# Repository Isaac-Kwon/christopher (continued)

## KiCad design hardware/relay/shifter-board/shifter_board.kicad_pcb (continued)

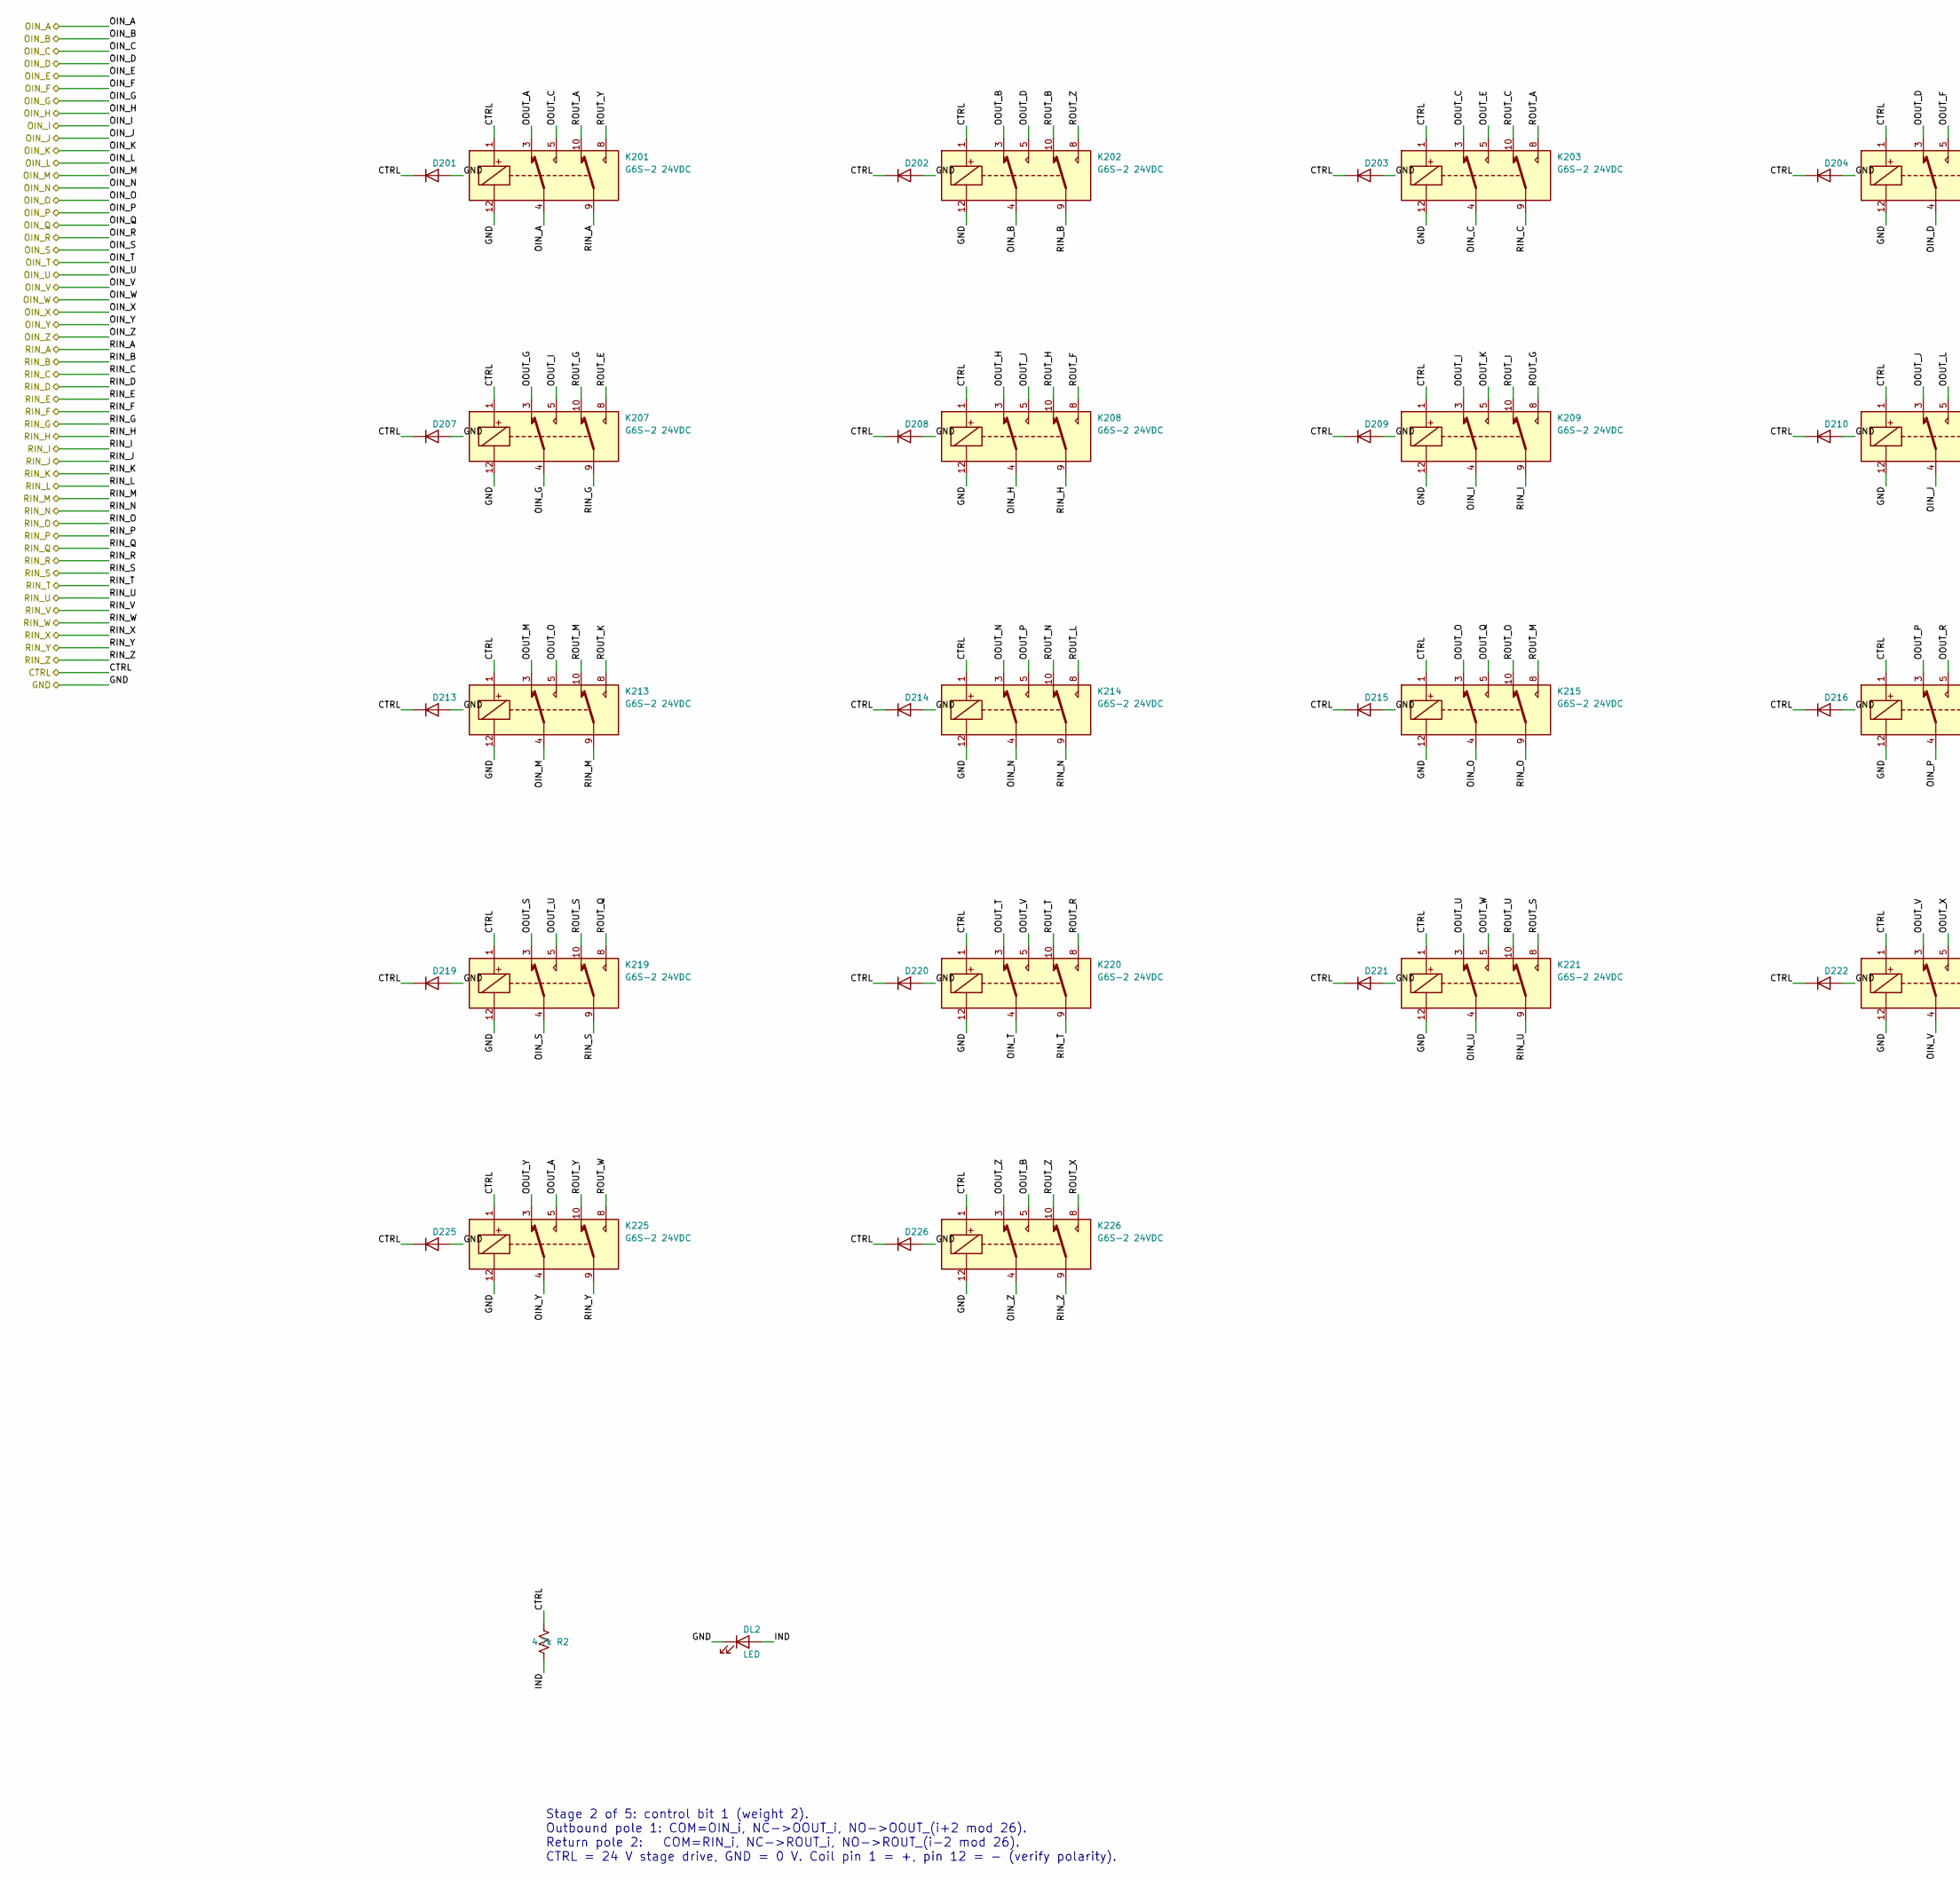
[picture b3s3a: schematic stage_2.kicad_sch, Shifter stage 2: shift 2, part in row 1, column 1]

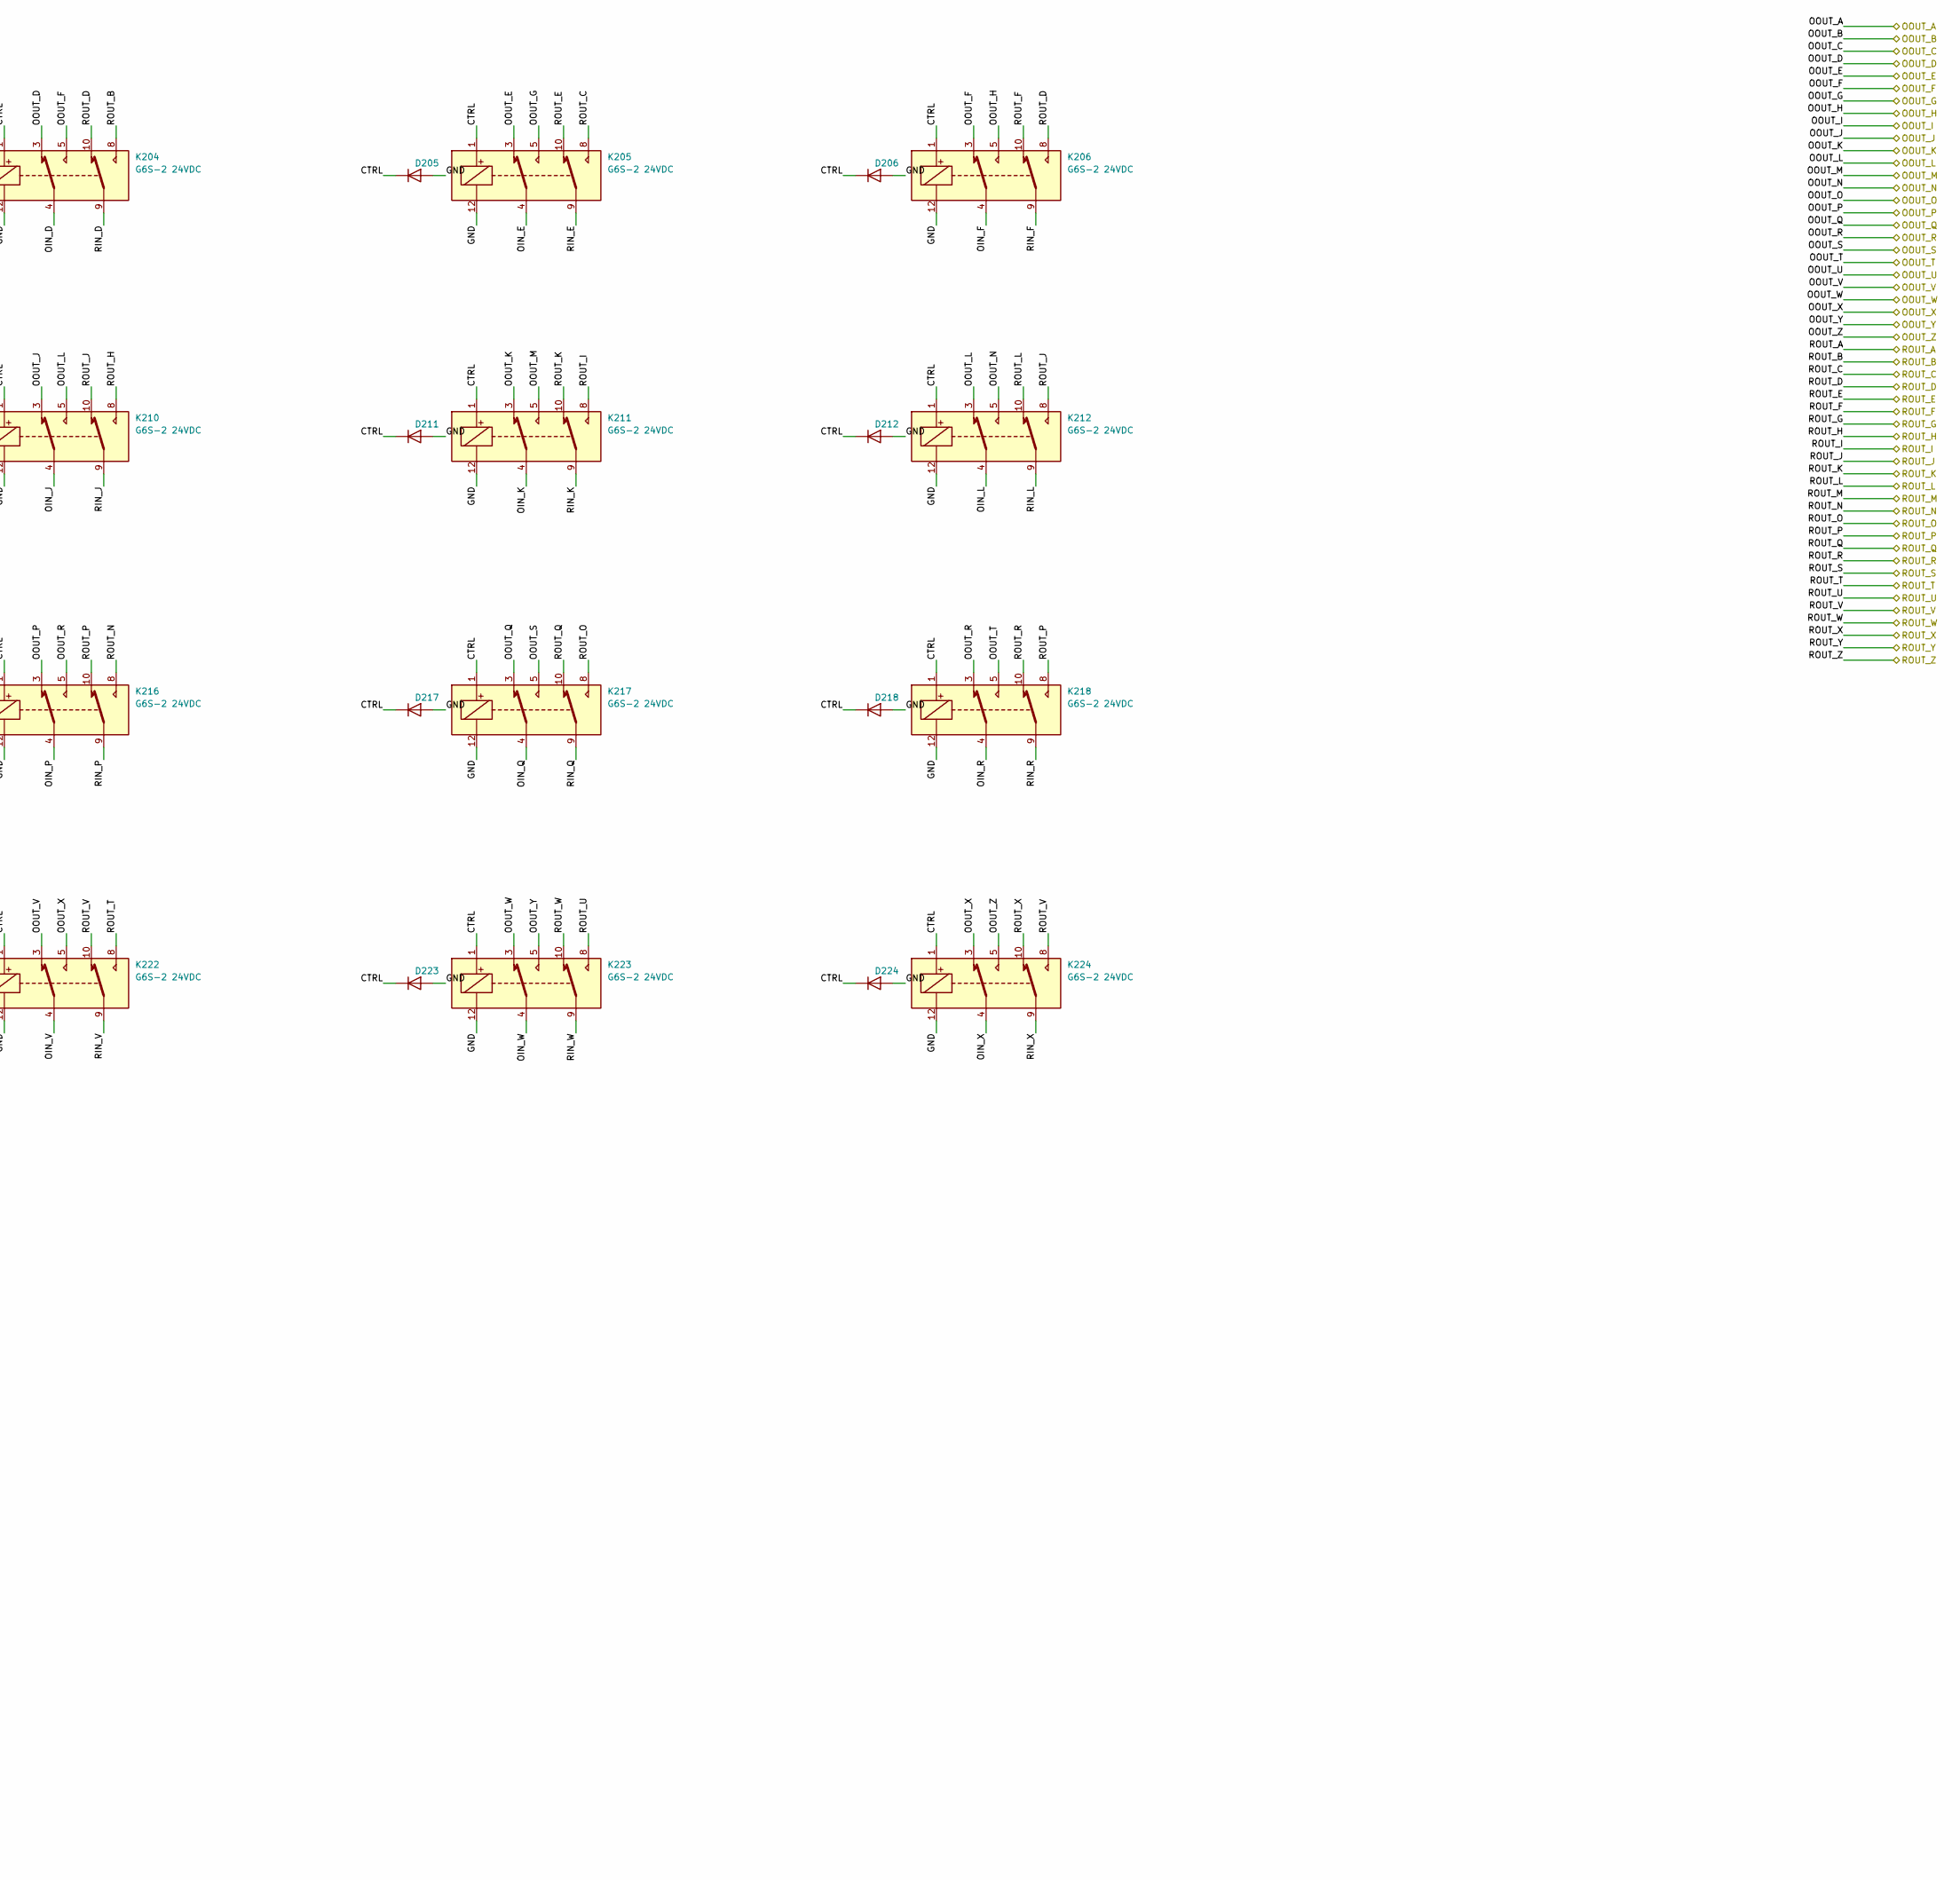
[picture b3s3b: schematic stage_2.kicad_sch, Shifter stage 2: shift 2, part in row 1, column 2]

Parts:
D201, D202, D203, D204, D205, D206, D207, D208, D209, D210, D211, D212, D213, D214, D215, D216, D217, D218, D219, D220, D221, D222, D223, D224, D225, D226: 1N4148W; D_SOD-123
DL2: LED; LED_0603_1608Metric
K201, K202, K203, K204, K205, K206, K207, K208, K209, K210, K211, K212, K213, K214, K215, K216, K217, K218, K219, K220, K221, K222, K223, K224, K225, K226: G6S-2 24VDC; Relay_DPDT_Omron_G6S-2
R2: 4.7k; R_0603_1608Metric

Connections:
/CTRL1: D201.1 (K), D202.1 (K), D203.1 (K), D204.1 (K), D205.1 (K), D206.1 (K), D207.1 (K), D208.1 (K), D209.1 (K), D210.1 (K), D211.1 (K), D212.1 (K), D213.1 (K), D214.1 (K), D215.1 (K), D216.1 (K), D217.1 (K), D218.1 (K), D219.1 (K), D220.1 (K), D221.1 (K), D222.1 (K), D223.1 (K), D224.1 (K), D225.1 (K), D226.1 (K), K201.1, K202.1, K203.1, K204.1, K205.1, K206.1, K207.1, K208.1, K209.1, K210.1, K211.1, K212.1, K213.1, K214.1, K215.1, K216.1, K217.1, K218.1, K219.1, K220.1, K221.1, K222.1, K223.1, K224.1, K225.1, K226.1, R2.1; also elsewhere on the board
/GND: D201.2 (A), D202.2 (A), D203.2 (A), D204.2 (A), D205.2 (A), D206.2 (A), D207.2 (A), D208.2 (A), D209.2 (A), D210.2 (A), D211.2 (A), D212.2 (A), D213.2 (A), D214.2 (A), D215.2 (A), D216.2 (A), D217.2 (A), D218.2 (A), D219.2 (A), D220.2 (A), D221.2 (A), D222.2 (A), D223.2 (A), D224.2 (A), D225.2 (A), D226.2 (A), DL2.1 (K), K201.12, K202.12, K203.12, K204.12, K205.12, K206.12, K207.12, K208.12, K209.12, K210.12, K211.12, K212.12, K213.12, K214.12, K215.12, K216.12, K217.12, K218.12, K219.12, K220.12, K221.12, K222.12, K223.12, K224.12, K225.12, K226.12; also elsewhere on the board
/O1_A: K201.4; also elsewhere on the board
/O1_B: K202.4; also elsewhere on the board
/O1_C: K203.4; also elsewhere on the board
/O1_D: K204.4; also elsewhere on the board
/O1_E: K205.4; also elsewhere on the board
/O1_F: K206.4; also elsewhere on the board
/O1_G: K207.4; also elsewhere on the board
/O1_H: K208.4; also elsewhere on the board
/O1_I: K209.4; also elsewhere on the board
/O1_J: K210.4; also elsewhere on the board
/O1_K: K211.4; also elsewhere on the board
/O1_L: K212.4; also elsewhere on the board
/O1_M: K213.4; also elsewhere on the board
/O1_N: K214.4; also elsewhere on the board
/O1_O: K215.4; also elsewhere on the board
/O1_P: K216.4; also elsewhere on the board
/O1_Q: K217.4; also elsewhere on the board
/O1_R: K218.4; also elsewhere on the board
/O1_S: K219.4; also elsewhere on the board
/O1_T: K220.4; also elsewhere on the board
/O1_U: K221.4; also elsewhere on the board
/O1_V: K222.4; also elsewhere on the board
/O1_W: K223.4; also elsewhere on the board
/O1_X: K224.4; also elsewhere on the board
/O1_Y: K225.4; also elsewhere on the board
/O1_Z: K226.4; also elsewhere on the board
/O2_A: K201.3, K225.5; also elsewhere on the board
/O2_B: K202.3, K226.5; also elsewhere on the board
/O2_C: K201.5, K203.3; also elsewhere on the board
/O2_D: K202.5, K204.3; also elsewhere on the board
/O2_E: K203.5, K205.3; also elsewhere on the board
/O2_F: K204.5, K206.3; also elsewhere on the board
/O2_G: K205.5, K207.3; also elsewhere on the board
/O2_H: K206.5, K208.3; also elsewhere on the board
/O2_I: K207.5, K209.3; also elsewhere on the board
/O2_J: K208.5, K210.3; also elsewhere on the board
/O2_K: K209.5, K211.3; also elsewhere on the board
/O2_L: K210.5, K212.3; also elsewhere on the board
/O2_M: K211.5, K213.3; also elsewhere on the board
/O2_N: K212.5, K214.3; also elsewhere on the board
/O2_O: K213.5, K215.3; also elsewhere on the board
/O2_P: K214.5, K216.3; also elsewhere on the board
/O2_Q: K215.5, K217.3; also elsewhere on the board
/O2_R: K216.5, K218.3; also elsewhere on the board
/O2_S: K217.5, K219.3; also elsewhere on the board
/O2_T: K218.5, K220.3; also elsewhere on the board
/O2_U: K219.5, K221.3; also elsewhere on the board
/O2_V: K220.5, K222.3; also elsewhere on the board
/O2_W: K221.5, K223.3; also elsewhere on the board
/O2_X: K222.5, K224.3; also elsewhere on the board
/O2_Y: K223.5, K225.3; also elsewhere on the board
/O2_Z: K224.5, K226.3; also elsewhere on the board
/R1_A: K201.9; also elsewhere on the board
/R1_B: K202.9; also elsewhere on the board
/R1_C: K203.9; also elsewhere on the board
/R1_D: K204.9; also elsewhere on the board
/R1_E: K205.9; also elsewhere on the board
/R1_F: K206.9; also elsewhere on the board
/R1_G: K207.9; also elsewhere on the board
/R1_H: K208.9; also elsewhere on the board
/R1_I: K209.9; also elsewhere on the board
/R1_J: K210.9; also elsewhere on the board
/R1_K: K211.9; also elsewhere on the board
/R1_L: K212.9; also elsewhere on the board
/R1_M: K213.9; also elsewhere on the board
/R1_N: K214.9; also elsewhere on the board
/R1_O: K215.9; also elsewhere on the board
/R1_P: K216.9; also elsewhere on the board
/R1_Q: K217.9; also elsewhere on the board
/R1_R: K218.9; also elsewhere on the board
/R1_S: K219.9; also elsewhere on the board
/R1_T: K220.9; also elsewhere on the board
/R1_U: K221.9; also elsewhere on the board
/R1_V: K222.9; also elsewhere on the board
/R1_W: K223.9; also elsewhere on the board
/R1_X: K224.9; also elsewhere on the board
/R1_Y: K225.9; also elsewhere on the board
/R1_Z: K226.9; also elsewhere on the board
/R2_A: K201.10, K203.8; also elsewhere on the board
/R2_B: K202.10, K204.8; also elsewhere on the board
/R2_C: K203.10, K205.8; also elsewhere on the board
/R2_D: K204.10, K206.8; also elsewhere on the board
/R2_E: K205.10, K207.8; also elsewhere on the board
/R2_F: K206.10, K208.8; also elsewhere on the board
/R2_G: K207.10, K209.8; also elsewhere on the board
/R2_H: K208.10, K210.8; also elsewhere on the board
/R2_I: K209.10, K211.8; also elsewhere on the board
/R2_J: K210.10, K212.8; also elsewhere on the board
/R2_K: K211.10, K213.8; also elsewhere on the board
/R2_L: K212.10, K214.8; also elsewhere on the board
/R2_M: K213.10, K215.8; also elsewhere on the board
/R2_N: K214.10, K216.8; also elsewhere on the board
/R2_O: K215.10, K217.8; also elsewhere on the board
/R2_P: K216.10, K218.8; also elsewhere on the board
/R2_Q: K217.10, K219.8; also elsewhere on the board
/R2_R: K218.10, K220.8; also elsewhere on the board
/R2_S: K219.10, K221.8; also elsewhere on the board
/R2_T: K220.10, K222.8; also elsewhere on the board
/R2_U: K221.10, K223.8; also elsewhere on the board
/R2_V: K222.10, K224.8; also elsewhere on the board
/R2_W: K223.10, K225.8; also elsewhere on the board
/R2_X: K224.10, K226.8; also elsewhere on the board
/R2_Y: K201.8, K225.10; also elsewhere on the board
/R2_Z: K202.8, K226.10; also elsewhere on the board
/STAGE_2/IND: DL2.2 (A), R2.2

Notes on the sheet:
Stage 2 of 5: control bit 1 (weight 2). Outbound pole 1: COM=OIN_i, NC->OOUT_i, NO->OOUT_(i+2 mod 26). Return pole 2: COM=RIN_i, NC->ROUT_i, NO->ROUT_(i-2 mod 26). CTRL = 24 V stage drive, GND = 0 V. Coil pin 1 = +, pin 12 = - (verify polarity).

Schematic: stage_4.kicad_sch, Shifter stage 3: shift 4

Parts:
D301, D302, D303, D304, D305, D306, D307, D308, D309, D310, D311, D312, D313, D314, D315, D316, D317, D318, D319, D320, D321, D322, D323, D324, D325, D326: 1N4148W; D_SOD-123
DL3: LED; LED_0603_1608Metric
K301, K302, K303, K304, K305, K306, K307, K308, K309, K310, K311, K312, K313, K314, K315, K316, K317, K318, K319, K320, K321, K322, K323, K324, K325, K326: G6S-2 24VDC; Relay_DPDT_Omron_G6S-2
R3: 4.7k; R_0603_1608Metric

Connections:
/CTRL2: D301.1 (K), D302.1 (K), D303.1 (K), D304.1 (K), D305.1 (K), D306.1 (K), D307.1 (K), D308.1 (K), D309.1 (K), D310.1 (K), D311.1 (K), D312.1 (K), D313.1 (K), D314.1 (K), D315.1 (K), D316.1 (K), D317.1 (K), D318.1 (K), D319.1 (K), D320.1 (K), D321.1 (K), D322.1 (K), D323.1 (K), D324.1 (K), D325.1 (K), D326.1 (K), K301.1, K302.1, K303.1, K304.1, K305.1, K306.1, K307.1, K308.1, K309.1, K310.1, K311.1, K312.1, K313.1, K314.1, K315.1, K316.1, K317.1, K318.1, K319.1, K320.1, K321.1, K322.1, K323.1, K324.1, K325.1, K326.1, R3.1; also elsewhere on the board
/GND: D301.2 (A), D302.2 (A), D303.2 (A), D304.2 (A), D305.2 (A), D306.2 (A), D307.2 (A), D308.2 (A), D309.2 (A), D310.2 (A), D311.2 (A), D312.2 (A), D313.2 (A), D314.2 (A), D315.2 (A), D316.2 (A), D317.2 (A), D318.2 (A), D319.2 (A), D320.2 (A), D321.2 (A), D322.2 (A), D323.2 (A), D324.2 (A), D325.2 (A), D326.2 (A), DL3.1 (K), K301.12, K302.12, K303.12, K304.12, K305.12, K306.12, K307.12, K308.12, K309.12, K310.12, K311.12, K312.12, K313.12, K314.12, K315.12, K316.12, K317.12, K318.12, K319.12, K320.12, K321.12, K322.12, K323.12, K324.12, K325.12, K326.12; also elsewhere on the board
/O2_A: K301.4; also elsewhere on the board
/O2_B: K302.4; also elsewhere on the board
/O2_C: K303.4; also elsewhere on the board
/O2_D: K304.4; also elsewhere on the board
/O2_E: K305.4; also elsewhere on the board
/O2_F: K306.4; also elsewhere on the board
/O2_G: K307.4; also elsewhere on the board
/O2_H: K308.4; also elsewhere on the board
/O2_I: K309.4; also elsewhere on the board
/O2_J: K310.4; also elsewhere on the board
/O2_K: K311.4; also elsewhere on the board
/O2_L: K312.4; also elsewhere on the board
/O2_M: K313.4; also elsewhere on the board
/O2_N: K314.4; also elsewhere on the board
/O2_O: K315.4; also elsewhere on the board
/O2_P: K316.4; also elsewhere on the board
/O2_Q: K317.4; also elsewhere on the board
/O2_R: K318.4; also elsewhere on the board
/O2_S: K319.4; also elsewhere on the board
/O2_T: K320.4; also elsewhere on the board
/O2_U: K321.4; also elsewhere on the board
/O2_V: K322.4; also elsewhere on the board
/O2_W: K323.4; also elsewhere on the board
/O2_X: K324.4; also elsewhere on the board
/O2_Y: K325.4; also elsewhere on the board
/O2_Z: K326.4; also elsewhere on the board
/O3_A: K301.3, K323.5; also elsewhere on the board
/O3_B: K302.3, K324.5; also elsewhere on the board
/O3_C: K303.3, K325.5; also elsewhere on the board
/O3_D: K304.3, K326.5; also elsewhere on the board
/O3_E: K301.5, K305.3; also elsewhere on the board
/O3_F: K302.5, K306.3; also elsewhere on the board
/O3_G: K303.5, K307.3; also elsewhere on the board
/O3_H: K304.5, K308.3; also elsewhere on the board
/O3_I: K305.5, K309.3; also elsewhere on the board
/O3_J: K306.5, K310.3; also elsewhere on the board
/O3_K: K307.5, K311.3; also elsewhere on the board
/O3_L: K308.5, K312.3; also elsewhere on the board
/O3_M: K309.5, K313.3; also elsewhere on the board
/O3_N: K310.5, K314.3; also elsewhere on the board
/O3_O: K311.5, K315.3; also elsewhere on the board
/O3_P: K312.5, K316.3; also elsewhere on the board
/O3_Q: K313.5, K317.3; also elsewhere on the board
/O3_R: K314.5, K318.3; also elsewhere on the board
/O3_S: K315.5, K319.3; also elsewhere on the board
/O3_T: K316.5, K320.3; also elsewhere on the board
/O3_U: K317.5, K321.3; also elsewhere on the board
/O3_V: K318.5, K322.3; also elsewhere on the board
/O3_W: K319.5, K323.3; also elsewhere on the board
/O3_X: K320.5, K324.3; also elsewhere on the board
/O3_Y: K321.5, K325.3; also elsewhere on the board
/O3_Z: K322.5, K326.3; also elsewhere on the board
/R2_A: K301.9; also elsewhere on the board
/R2_B: K302.9; also elsewhere on the board
/R2_C: K303.9; also elsewhere on the board
/R2_D: K304.9; also elsewhere on the board
/R2_E: K305.9; also elsewhere on the board
/R2_F: K306.9; also elsewhere on the board
/R2_G: K307.9; also elsewhere on the board
/R2_H: K308.9; also elsewhere on the board
/R2_I: K309.9; also elsewhere on the board
/R2_J: K310.9; also elsewhere on the board
/R2_K: K311.9; also elsewhere on the board
/R2_L: K312.9; also elsewhere on the board
/R2_M: K313.9; also elsewhere on the board
/R2_N: K314.9; also elsewhere on the board
/R2_O: K315.9; also elsewhere on the board
/R2_P: K316.9; also elsewhere on the board
/R2_Q: K317.9; also elsewhere on the board
/R2_R: K318.9; also elsewhere on the board
/R2_S: K319.9; also elsewhere on the board
/R2_T: K320.9; also elsewhere on the board
/R2_U: K321.9; also elsewhere on the board
/R2_V: K322.9; also elsewhere on the board
/R2_W: K323.9; also elsewhere on the board
/R2_X: K324.9; also elsewhere on the board
/R2_Y: K325.9; also elsewhere on the board
/R2_Z: K326.9; also elsewhere on the board
/R3_A: K301.10, K305.8; also elsewhere on the board
/R3_B: K302.10, K306.8; also elsewhere on the board
/R3_C: K303.10, K307.8; also elsewhere on the board
/R3_D: K304.10, K308.8; also elsewhere on the board
/R3_E: K305.10, K309.8; also elsewhere on the board
/R3_F: K306.10, K310.8; also elsewhere on the board
/R3_G: K307.10, K311.8; also elsewhere on the board
/R3_H: K308.10, K312.8; also elsewhere on the board
/R3_I: K309.10, K313.8; also elsewhere on the board
/R3_J: K310.10, K314.8; also elsewhere on the board
/R3_K: K311.10, K315.8; also elsewhere on the board
/R3_L: K312.10, K316.8; also elsewhere on the board
/R3_M: K313.10, K317.8; also elsewhere on the board
/R3_N: K314.10, K318.8; also elsewhere on the board
/R3_O: K315.10, K319.8; also elsewhere on the board
/R3_P: K316.10, K320.8; also elsewhere on the board
/R3_Q: K317.10, K321.8; also elsewhere on the board
/R3_R: K318.10, K322.8; also elsewhere on the board
/R3_S: K319.10, K323.8; also elsewhere on the board
/R3_T: K320.10, K324.8; also elsewhere on the board
/R3_U: K321.10, K325.8; also elsewhere on the board
/R3_V: K322.10, K326.8; also elsewhere on the board
/R3_W: K301.8, K323.10; also elsewhere on the board
/R3_X: K302.8, K324.10; also elsewhere on the board
/R3_Y: K303.8, K325.10; also elsewhere on the board
/R3_Z: K304.8, K326.10; also elsewhere on the board
/STAGE_4/IND: DL3.2 (A), R3.2

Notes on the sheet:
Stage 3 of 5: control bit 2 (weight 4). Outbound pole 1: COM=OIN_i, NC->OOUT_i, NO->OOUT_(i+4 mod 26). Return pole 2: COM=RIN_i, NC->ROUT_i, NO->ROUT_(i-4 mod 26). CTRL = 24 V stage drive, GND = 0 V. Coil pin 1 = +, pin 12 = - (verify polarity).

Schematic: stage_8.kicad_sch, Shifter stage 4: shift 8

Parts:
D401, D402, D403, D404, D405, D406, D407, D408, D409, D410, D411, D412, D413, D414, D415, D416, D417, D418, D419, D420, D421, D422, D423, D424, D425, D426: 1N4148W; D_SOD-123
DL4: LED; LED_0603_1608Metric
K401, K402, K403, K404, K405, K406, K407, K408, K409, K410, K411, K412, K413, K414, K415, K416, K417, K418, K419, K420, K421, K422, K423, K424, K425, K426: G6S-2 24VDC; Relay_DPDT_Omron_G6S-2
R4: 4.7k; R_0603_1608Metric

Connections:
/CTRL3: D401.1 (K), D402.1 (K), D403.1 (K), D404.1 (K), D405.1 (K), D406.1 (K), D407.1 (K), D408.1 (K), D409.1 (K), D410.1 (K), D411.1 (K), D412.1 (K), D413.1 (K), D414.1 (K), D415.1 (K), D416.1 (K), D417.1 (K), D418.1 (K), D419.1 (K), D420.1 (K), D421.1 (K), D422.1 (K), D423.1 (K), D424.1 (K), D425.1 (K), D426.1 (K), K401.1, K402.1, K403.1, K404.1, K405.1, K406.1, K407.1, K408.1, K409.1, K410.1, K411.1, K412.1, K413.1, K414.1, K415.1, K416.1, K417.1, K418.1, K419.1, K420.1, K421.1, K422.1, K423.1, K424.1, K425.1, K426.1, R4.1; also elsewhere on the board
/GND: D401.2 (A), D402.2 (A), D403.2 (A), D404.2 (A), D405.2 (A), D406.2 (A), D407.2 (A), D408.2 (A), D409.2 (A), D410.2 (A), D411.2 (A), D412.2 (A), D413.2 (A), D414.2 (A), D415.2 (A), D416.2 (A), D417.2 (A), D418.2 (A), D419.2 (A), D420.2 (A), D421.2 (A), D422.2 (A), D423.2 (A), D424.2 (A), D425.2 (A), D426.2 (A), DL4.1 (K), K401.12, K402.12, K403.12, K404.12, K405.12, K406.12, K407.12, K408.12, K409.12, K410.12, K411.12, K412.12, K413.12, K414.12, K415.12, K416.12, K417.12, K418.12, K419.12, K420.12, K421.12, K422.12, K423.12, K424.12, K425.12, K426.12; also elsewhere on the board
/O3_A: K401.4; also elsewhere on the board
/O3_B: K402.4; also elsewhere on the board
/O3_C: K403.4; also elsewhere on the board
/O3_D: K404.4; also elsewhere on the board
/O3_E: K405.4; also elsewhere on the board
/O3_F: K406.4; also elsewhere on the board
/O3_G: K407.4; also elsewhere on the board
/O3_H: K408.4; also elsewhere on the board
/O3_I: K409.4; also elsewhere on the board
/O3_J: K410.4; also elsewhere on the board
/O3_K: K411.4; also elsewhere on the board
/O3_L: K412.4; also elsewhere on the board
/O3_M: K413.4; also elsewhere on the board
/O3_N: K414.4; also elsewhere on the board
/O3_O: K415.4; also elsewhere on the board
/O3_P: K416.4; also elsewhere on the board
/O3_Q: K417.4; also elsewhere on the board
/O3_R: K418.4; also elsewhere on the board
/O3_S: K419.4; also elsewhere on the board
/O3_T: K420.4; also elsewhere on the board
/O3_U: K421.4; also elsewhere on the board
/O3_V: K422.4; also elsewhere on the board
/O3_W: K423.4; also elsewhere on the board
/O3_X: K424.4; also elsewhere on the board
/O3_Y: K425.4; also elsewhere on the board
/O3_Z: K426.4; also elsewhere on the board
/O4_A: K401.3, K419.5; also elsewhere on the board
/O4_B: K402.3, K420.5; also elsewhere on the board
/O4_C: K403.3, K421.5; also elsewhere on the board
/O4_D: K404.3, K422.5; also elsewhere on the board
/O4_E: K405.3, K423.5; also elsewhere on the board
/O4_F: K406.3, K424.5; also elsewhere on the board
/O4_G: K407.3, K425.5; also elsewhere on the board
/O4_H: K408.3, K426.5; also elsewhere on the board
/O4_I: K401.5, K409.3; also elsewhere on the board
/O4_J: K402.5, K410.3; also elsewhere on the board
/O4_K: K403.5, K411.3; also elsewhere on the board
/O4_L: K404.5, K412.3; also elsewhere on the board
/O4_M: K405.5, K413.3; also elsewhere on the board
/O4_N: K406.5, K414.3; also elsewhere on the board
/O4_O: K407.5, K415.3; also elsewhere on the board
/O4_P: K408.5, K416.3; also elsewhere on the board
/O4_Q: K409.5, K417.3; also elsewhere on the board
/O4_R: K410.5, K418.3; also elsewhere on the board
/O4_S: K411.5, K419.3; also elsewhere on the board
/O4_T: K412.5, K420.3; also elsewhere on the board
/O4_U: K413.5, K421.3; also elsewhere on the board
/O4_V: K414.5, K422.3; also elsewhere on the board
/O4_W: K415.5, K423.3; also elsewhere on the board
/O4_X: K416.5, K424.3; also elsewhere on the board
/O4_Y: K417.5, K425.3; also elsewhere on the board
/O4_Z: K418.5, K426.3; also elsewhere on the board
/R3_A: K401.9; also elsewhere on the board
/R3_B: K402.9; also elsewhere on the board
/R3_C: K403.9; also elsewhere on the board
/R3_D: K404.9; also elsewhere on the board
/R3_E: K405.9; also elsewhere on the board
/R3_F: K406.9; also elsewhere on the board
/R3_G: K407.9; also elsewhere on the board
/R3_H: K408.9; also elsewhere on the board
/R3_I: K409.9; also elsewhere on the board
/R3_J: K410.9; also elsewhere on the board
/R3_K: K411.9; also elsewhere on the board
/R3_L: K412.9; also elsewhere on the board
/R3_M: K413.9; also elsewhere on the board
/R3_N: K414.9; also elsewhere on the board
/R3_O: K415.9; also elsewhere on the board
/R3_P: K416.9; also elsewhere on the board
/R3_Q: K417.9; also elsewhere on the board
/R3_R: K418.9; also elsewhere on the board
/R3_S: K419.9; also elsewhere on the board
/R3_T: K420.9; also elsewhere on the board
/R3_U: K421.9; also elsewhere on the board
/R3_V: K422.9; also elsewhere on the board
/R3_W: K423.9; also elsewhere on the board
/R3_X: K424.9; also elsewhere on the board
/R3_Y: K425.9; also elsewhere on the board
/R3_Z: K426.9; also elsewhere on the board
/R4_A: K401.10, K409.8; also elsewhere on the board
/R4_B: K402.10, K410.8; also elsewhere on the board
/R4_C: K403.10, K411.8; also elsewhere on the board
/R4_D: K404.10, K412.8; also elsewhere on the board
/R4_E: K405.10, K413.8; also elsewhere on the board
/R4_F: K406.10, K414.8; also elsewhere on the board
/R4_G: K407.10, K415.8; also elsewhere on the board
/R4_H: K408.10, K416.8; also elsewhere on the board
/R4_I: K409.10, K417.8; also elsewhere on the board
/R4_J: K410.10, K418.8; also elsewhere on the board
/R4_K: K411.10, K419.8; also elsewhere on the board
/R4_L: K412.10, K420.8; also elsewhere on the board
/R4_M: K413.10, K421.8; also elsewhere on the board
/R4_N: K414.10, K422.8; also elsewhere on the board
/R4_O: K415.10, K423.8; also elsewhere on the board
/R4_P: K416.10, K424.8; also elsewhere on the board
/R4_Q: K417.10, K425.8; also elsewhere on the board
/R4_R: K418.10, K426.8; also elsewhere on the board
/R4_S: K401.8, K419.10; also elsewhere on the board
/R4_T: K402.8, K420.10; also elsewhere on the board
/R4_U: K403.8, K421.10; also elsewhere on the board
/R4_V: K404.8, K422.10; also elsewhere on the board
/R4_W: K405.8, K423.10; also elsewhere on the board
/R4_X: K406.8, K424.10; also elsewhere on the board
/R4_Y: K407.8, K425.10; also elsewhere on the board
/R4_Z: K408.8, K426.10; also elsewhere on the board
/STAGE_8/IND: DL4.2 (A), R4.2

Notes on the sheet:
Stage 4 of 5: control bit 3 (weight 8). Outbound pole 1: COM=OIN_i, NC->OOUT_i, NO->OOUT_(i+8 mod 26). Return pole 2: COM=RIN_i, NC->ROUT_i, NO->ROUT_(i-8 mod 26). CTRL = 24 V stage drive, GND = 0 V. Coil pin 1 = +, pin 12 = - (verify polarity).
